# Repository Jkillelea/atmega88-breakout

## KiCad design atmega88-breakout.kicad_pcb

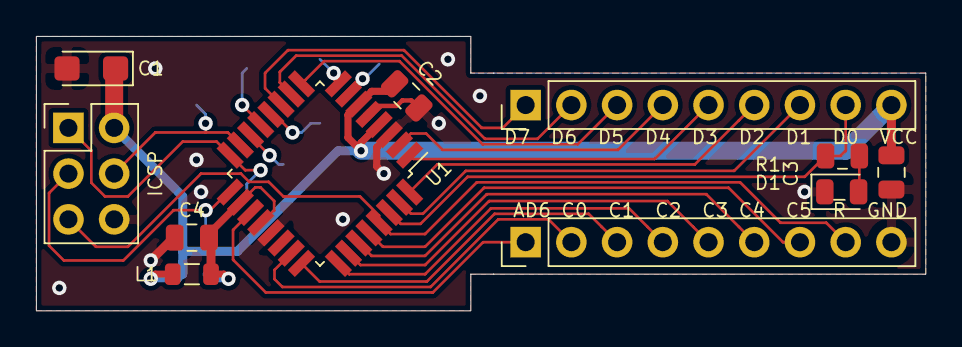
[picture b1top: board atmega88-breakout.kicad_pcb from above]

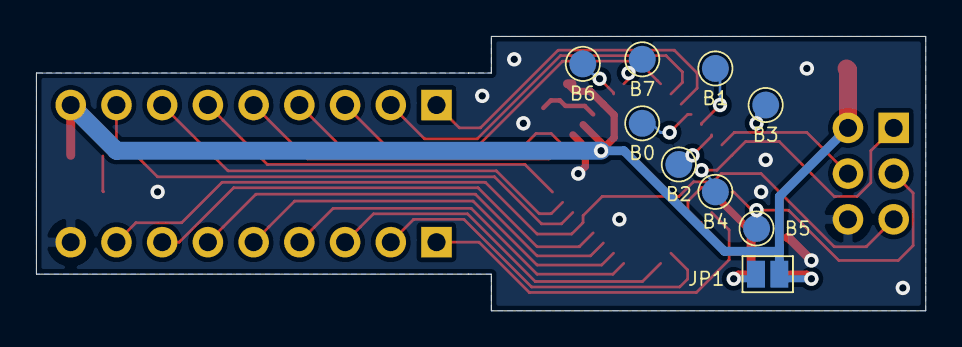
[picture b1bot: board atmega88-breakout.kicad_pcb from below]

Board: 2 copper layers, 49.4 x 15.2 mm, 20 parts (9 on the bottom side), 28 nets.

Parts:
B0, B1, B2, B3, B4, B5, B6, B7: TestPoint; TestPoint_Pad_D1.5mm
C1: 10u; CP_EIA-3216-18_Kemet-A
C2, C3, C4: 100nF; C_0805_2012Metric
D1: LED_Small; LED_0805_2012Metric
ICSP: ICSP Header; PinHeader_2x03_P2.54mm_Vertical
J1, J3: Conn_01x09; PinHeader_1x09_P2.54mm_Vertical
JP1: SolderJumper_2_Open; SolderJumper-2_P1.3mm_Open_Pad1.0x1.5mm
L1: L_Small; L_0805_2012Metric
R1: 1k; R_0805_2012Metric
U1: ATmega88PA-AU; TQFP-32_7x7mm_P0.8mm

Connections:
/B0: B0.1, U1.12
/B1: B1.1, U1.13
/B2: B2.1, U1.14
/B3: B3.1, ICSP.4, U1.15
/B4: B4.1, ICSP.1, U1.16
/B5: B5.1, ICSP.3, U1.17
/B6: B6.1, U1.7
/B7: B7.1, U1.8
/C0: J1.2, U1.23
/C1: J1.3, U1.24
/C2: J1.4, U1.25
/C3: J1.5, U1.26
/C4: J1.6, U1.27
/C5: J1.7, U1.28
/C6: ICSP.5, J1.8, U1.29
/D0: J3.8, R1.1, U1.30
/D1: J3.7, U1.31
/D2: J3.6, U1.32
/D3: J3.5, U1.1
/D4: J3.4, U1.2
/D5: J3.3, U1.9
/D6: J3.2, U1.10
/D7: J3.1, U1.11
ADC6: J1.1, U1.19
GND: C1.2, C2.1, C3.1, C4.1, D1.1, ICSP.6, J1.9, U1.3, U1.5, U1.21
unnamed: D1.2, R1.2
VAA: C4.2, JP1.2, L1.2, U1.18, U1.20
VCC: C1.1, C2.2, C3.2, ICSP.2, J3.9, JP1.1, L1.1, U1.4, U1.6

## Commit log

2020-12-17 First
2020-12-22 Route all IO, add user LED, need to add power headers
2020-12-23 Misc files
2020-12-26 Rev A release (ordered)
2021-02-06 Add everything idk
